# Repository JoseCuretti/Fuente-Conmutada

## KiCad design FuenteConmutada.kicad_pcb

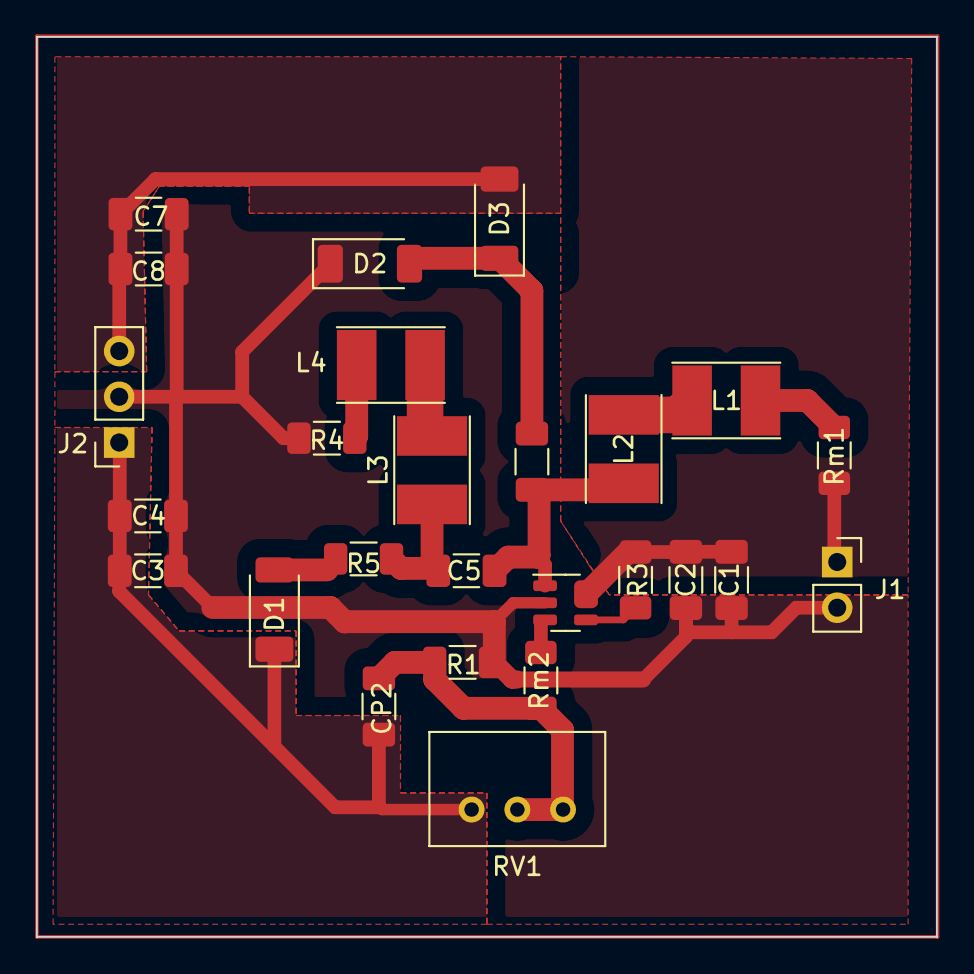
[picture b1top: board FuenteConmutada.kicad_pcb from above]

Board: 2 copper layers, 50.0 x 50.0 mm, 26 parts (0 on the bottom side), 15 nets.

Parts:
C1, C2, C3, C4, C7, C8: 22uF; C_1206_3216Metric_Pad1.33x1.80mm_HandSolder
C5: 1uF; C_1206_3216Metric_Pad1.33x1.80mm_HandSolder
CP1: 1uF; C_1206_3216Metric_Pad1.33x1.80mm_HandSolder
CP2: 22uF; C_1206_3216Metric_Pad1.33x1.80mm_HandSolder
D1, D2, D3: D_Schottky; D_SOD-128
J1: Conn_01x02_Socket; PinSocket_1x02_P2.54mm_Vertical
J2: Conn_01x03_Socket; PinSocket_1x03_P2.54mm_Vertical
L1, L2, L3, L4: 10uH; L_Taiyo-Yuden_NR-40xx_HandSoldering
R1: 5k; R_1206_3216Metric_Pad1.30x1.75mm_HandSolder
R3, R4, R5: R; R_1206_3216Metric_Pad1.30x1.75mm_HandSolder
RV1: 100k; Potentiometer_Bourns_3299W_Vertical
Rm1, Rm2: R; R_1206_3216Metric_Pad1.30x1.75mm_HandSolder
U1: MT3608; SOT-23-6

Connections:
/Vin: C1.2, C2.2, J1.1, R3.1, Rm1.1, U1.5 (IN)
/Vo+: C3.2, C4.2, CP2.2, D1.1 (K), J2.1, RV1.1
/Vo-: C7.2, C8.2, D3.2 (A), J2.3
GND: C1.1, C2.1, C3.1, C4.1, C7.1, C8.1, D2.1 (K), J1.2, J2.2, R1.2, R4.1, U1.2 (GND)
unnamed: C5.1, L3.1, R5.1
unnamed: CP2.1, R1.1, RV1.2, RV1.3, Rm2.1
unnamed: D1.2 (A), R5.2
unnamed: CP1.2, D2.2 (A), D3.1 (K)
unnamed: L1.1, Rm1.2
unnamed: L1.2, L2.1
unnamed: L3.2, L4.1
unnamed: L4.2, R4.2
unnamed: R3.2, U1.4 (EN)
unnamed: Rm2.2, U1.3 (FB)
unnamed: C5.2, CP1.1, L2.2, U1.1 (SW)

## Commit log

2024-04-07 Archivos Base del proyecto KiCad
2024-04-07 Titulo en Esquematico
2024-04-11 Simulación en PSpice + esquemático
2024-04-11 USB C de entrada
    Revisar huella para no cometer el mismo error que en la placa del PIC
2024-04-11 LT1930A en LTspice.
2024-04-12 avance en ruteo
2024-04-12 LTSpice LMR64010
2024-04-13 Esquematico 3in1 + Simbolo LMR64010 + Simu LT1930
    Esquematico placa de prueba Boost-SEPIC-Fuente partida;
    Simbolo para simulacion de LMR64010(xxx.asy debe estar en la misma carpeta);
    Simulacion pasos del potenciometro, permite seleccionar el valor del pote(depende del valor de R2, L, RL)
2024-04-13 Simu LT1930 fuente partida
2024-04-16 Correccion para simulacion 64010
    Cree un simbolo aparte con las misma dimensiones y pines, y ejecuta el modelo spice mediante directiva include
2024-04-19 pote y área
    Cambios en huella de pote multi , 3 pines alineados y agregado del área de 5cm x 5cm
2024-04-19 Cambios PCB+Esquematico
    Huellas nuevas para inductores, diodos.
    Correccion de diodo mal ubicado.
    Se añadio R en serie con inductores 3 y 4, capacitor para compensacion, un segundo capacitor para salida Vo-.
    Planos de GND, Vin, Vo+ y Vo-. Y tambien se agrandaron algunas pistas.
2024-04-19 PCB+Esquematico(actualizacion)
    Se agrego R en serie con el diodo D1.
    Y se habia agregado anteriormente una modificación sobre la huella del regulador.
2024-04-25 Modelos 3D diodos e inductores 4mm x 4mm
2024-04-26 Ajustes planos y tracks
    Agrandar Margen a 40mils de los planos
    Cambiar Rmed de lado del inductor (hacia Vin)
    Cambiar Pos Inductores, mas cerca de SW
    Aumentar a 50mils todos los tracks que no esten embutidos en planos
    Puente en GND/Vfedback para no pasar debajo del SOT23
    -Verificar cambios y poner Listo en la wiki
2024-04-30 Acomodo de R1
    Movi ligeramente R1 para aumentar la distancia a la pista GND
2024-05-14 Simu LTspice LMR62421X + Archivos para PCB
    Archivos PCB CAT(con alivios termicos) y SAT(sin alivios termicos)
2024-05-16 Simus
2024-08-09 Create Version-10W.md
    Inicio de nueva versión de fuente conmutada 10W
